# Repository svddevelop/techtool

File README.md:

( [RU](./README-RU.md) )
( [EN](./README.md) )
---

### TechTool

A tool built on the Raspberry Pi platform for monitoring vehicle electrical systems. It connects via the OBD2 port and uses onboard power. A smartphone, tablet, or laptop is intended to be used as the display.
Access is provided via WiFi (the Raspberry Pi works as an access point). Communication is done through a web interface or via an SSH terminal connection.

---

### Image

The image can be found in the `img` subdirectory. It is written to a USB drive of at least 4GB. It is based on the latest version of Raspberry Pi OS 64-bit.

***

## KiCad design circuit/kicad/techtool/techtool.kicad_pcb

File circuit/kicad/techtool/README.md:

( [RU](./README-RU.md) )
( [DE](./README-DE.md) )
---

### Simplified Diagram

Everything is assembled using ready-made modules, so the diagram is greatly simplified.

The diagram shows the connections between the Raspberry Pi connector and the MCP2515+TJA1050 module. The module is powered from the RPI +5V pin. However, the module has a design flaw and requires modification. The power for the TJA1050 should remain +5V, while the MCP2515 requires +3V3. The RPi pinout operates at 3 volts, is tolerant to 5 volts due to internal suppressors, and does not require a level converter.

Therefore, the MCP2515+TJA1050 module has undergone some modifications. The traces on both sides were cut, the contacts were cleaned, and an AS1117-3V3 chip was soldered to step down the voltage from 5 volts to 3 volts.

>**Warning:**
When connecting the circuit to the OBD2 onboard connector, do not forget to include jumper J1 (120Ω terminator).

Since the modules need to be powered from the onboard power supply of the OBD2 connector, the MP1854 was chosen as the STEP-Down regulator, which can operate with an input voltage range of 5 to 36 volts. Additionally, it provides short-circuit protection for a short duration.

Before connecting the regulator to the RPi, it is necessary to set the output voltage using the potentiometer to the range of 5 volts. Simply connect it to the RPi +5V and GND pins. Also, the GND pin must be connected to pin 4 of the OBD2 connector, and the In+ pin of the regulator must be connected to pin 16 of the OBD2 connector.

>**Warning:**
The pin numbering on the connector is shown correctly in the diagram, but in reality, pins 9 to 16 are in reverse order, and pin 16 is located below pin 1.

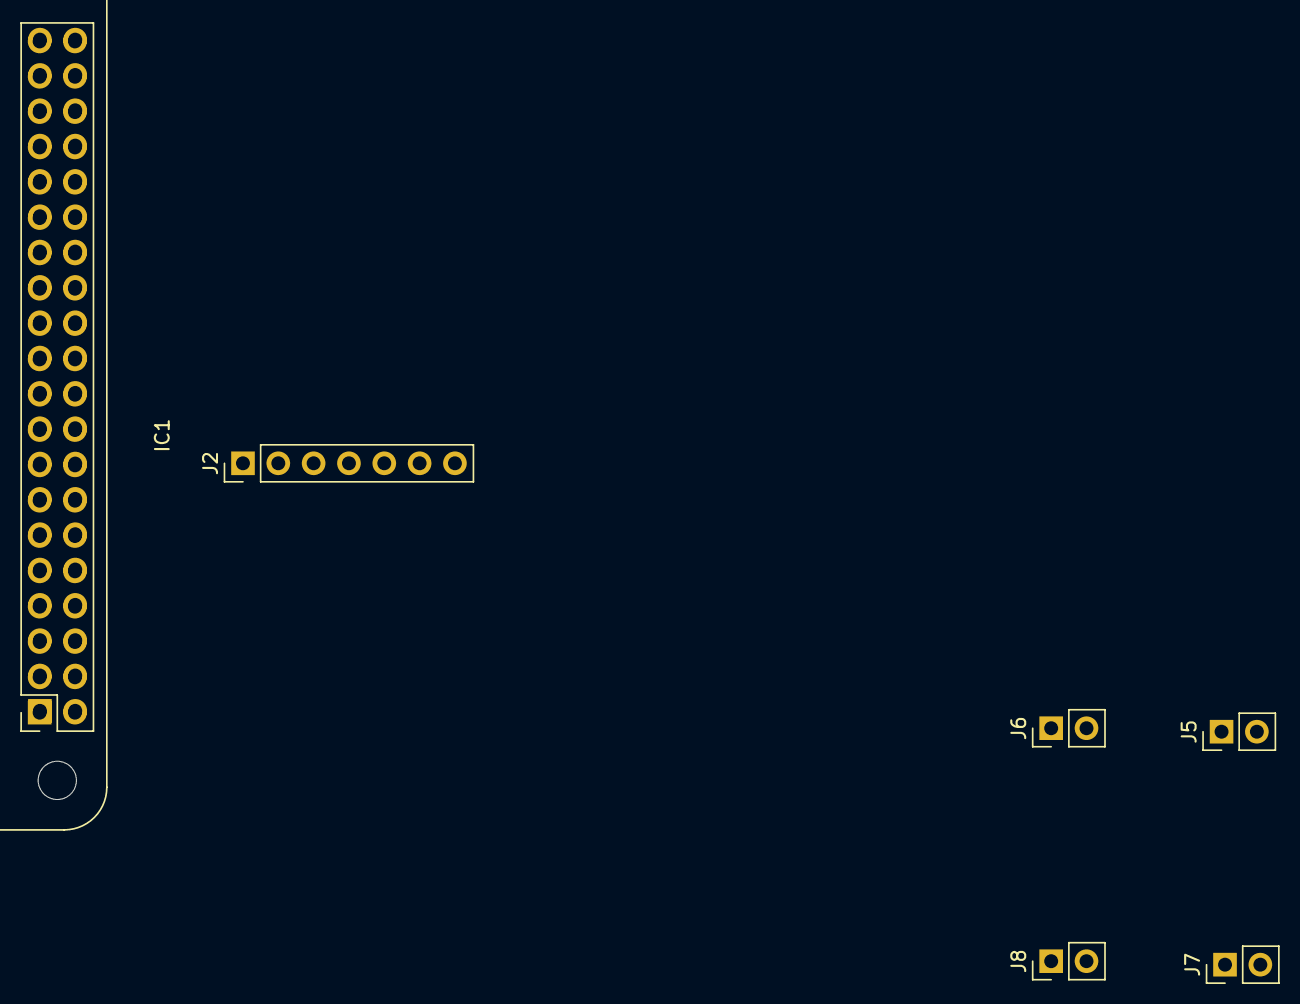
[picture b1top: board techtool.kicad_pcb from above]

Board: 2 copper layers, 7 parts (1 on the bottom side), 8 nets, no tracks yet.

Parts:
IC1: Raspberry_Pi_Zero_W_(v1.3); Raspberry_Pi_Zero_Socketed_THT_FaceDown_MountingHoles
J1: Raspberry_Pi_2_3; PinHeader_2x20_P2.54mm_Vertical
J2: MCP2515+TJA1050; PinHeader_1x07_P2.54mm_Vertical
J5: VCC; PinHeader_1x02_P2.54mm_Vertical
J6: GND; PinHeader_1x02_P2.54mm_Vertical
J7: In+; PinHeader_1x02_P2.54mm_Vertical
J8: In-; PinHeader_1x02_P2.54mm_Vertical

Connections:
CS: J1.24 (~CE0/GPIO8), J2.3
GND: J1.6 (GND), J1.9 (GND), J1.14 (GND), J1.20 (GND), J1.25 (GND), J1.30 (GND), J1.34 (GND), J1.39 (GND), J2.2, J6.2
INT: J1.22 (GPIO25), J2.7
unnamed: J1.1 (3V3), J1.17 (3V3)
SCK: J1.23 (SCLK0/GPIO11), J2.6
SI: J1.19 (MOSI0/GPIO10), J2.5
SO: J1.21 (MISO0/GPIO9), J2.4
VCC: J1.2 (5V), J1.4 (5V), J2.1, J5.1

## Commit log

2025-01-14 crate_connect_wifi; csws.conf
2025-01-14 csws ver 0.0.0.153 - at the 'shell' must be show only first word
2025-01-14 shellcomand and fullshellcomand
2025-01-16 README correction with Debian version
2025-01-16 csws ver. 0.0.0.169
2025-01-16 Image with csws version 0.0.0.169
2025-01-16 csws as service& better to run as default user
2025-01-17 can-utils menu with many speed settings
2025-01-18 can0 menu with info
